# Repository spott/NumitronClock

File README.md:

# Numitron Clock

Top-board schematic and PCB layout for the four-tube clock described in the Obsidian note `electronics/Numitron Clock/Numitron Clock.md`, read on 2026-09-18. The detailed top-board decisions in that note supersede its older, general power and interconnect descriptions.

Open **[NumitronTop.kicad_pro](hardware/top-board/NumitronTop.kicad_pro)** in KiCad. The design was captured and checked with **KiCad 10.0.5**. All schematic symbols are included in the project-local library and embedded in the sheets.

## Review this revision

- [Power and inter-board interface](review/NumitronTop.svg)
- [Control and light sensor](review/NumitronTop-Logic%20_%20ambient%20light.svg)
- [Four tube drivers](review/NumitronTop-Four%20tube%20drivers.svg)
- [Connector and firmware contract](docs/interface.md)
- [Electrical design notes](docs/design.md)
- [Preliminary BOM](docs/bom.md)
- [Socket drawing and dimensions](docs/socket.md)
- [Provisional socket footprint](review/GZC9-A_B9A_Provisional.svg)
- [Top layout](review/NumitronTop-top.png), [underside layout](review/NumitronTop-bottom.png) and [dimensions / review notes](docs/placement.md)
- [Bring-up and ordering checks](docs/bring-up.md)
- [Archived component datasheets](datasheets/README.md)
- [ERC result](review/erc.rpt) and [exported-netlist audit](review/connectivity.txt)

The top board is placed and routed on a **110 × 40 mm working outline** with all 55 schematic parts, four M2.5 mounting positions, local power distribution and ground copper on both faces. The extra depth provides a separate underside strip for the wide SOIC drivers. The [layout notes](docs/placement.md) explain component placement, the perpendicular underside connector orientation and review process.

The GZC9-A socket footprint remains **provisional**, as explicitly authorized on 2026-09-25: 18 mm assumed tail circle, 0.5 mm estimated terminal thickness, 2.5 mm plated holes and 3.8 mm copper lands. Verify physical fit before ordering. Enclosure/cable fit, exact capacitor order codes and hardware measurements also remain assembly/release checks. **WWVB versus GPS belongs to the bottom board.**

The owner confirms the actual tubes are **marked DR2000 and have prefix decimal points**. The archived RCA table assigns that feature to DR2010 instead. The design preserves the requested HH.MM display and routes the eighth channel to pin 1; verify that decimal connection on the actual tubes before enabling it.

## Development

### ES100 time-source test firmware

The reusable async ES100 driver and Pico 2 breadboard program live in
[`firmware/`](firmware/README.md). Build and check them with the pinned firmware
toolchain (Rust/Cargo, Pico 2 target, flip-link and picotool are supplied by Nix):

```sh
nix develop .#firmware --command bash scripts/check_firmware.sh
```

The generated UF2 is `firmware/target/pico2-es100.uf2`. See the firmware guide for
wiring, BOOTSEL flashing, USB logs and the hardware test handoff. Physical
reception has not been validated; this does not decide WWVB versus GPS.

### Hardware tooling

Use the pinned Nix flake; no global package installation is required. KiCad is supplied by the existing local application installation on macOS. The flake pins the supporting Python, Poppler, SVG-rendering and local Freerouting tools, not that external KiCad application.

```sh
nix develop
bash scripts/review.sh
```

The review command runs KiCad ERC, audits the saved schematic's netlist and provisional socket footprint, exports schematic and footprint SVGs, and renders inspection PNGs under ignored `tmp/render/`. It does not regenerate or overwrite the schematic or footprint. Source PDFs and the socket drawing are archived in Git with their provenance and hashes.

`scripts/build_schematic.py --write` records the initial schematic capture and is deliberately opt-in: it **overwrites the native KiCad files**. After editing in KiCad, preserve those edits; reconcile the generator before using it again.

`hardware/top-board/socket-footprint.json` records the socket assumptions. `scripts/build_socket_footprint.py --write` captures them into the project-local `Numitron.pretty` library; reconcile manual footprint edits before regenerating. The schematic assigns `Numitron:GZC9-A_B9A_Provisional` to V1-V4.

`nix develop --command bash scripts/review_placement.sh` checks the saved PCB against the netlist, runs DRC with schematic parity and generates the top/bottom review drawings. It does not regenerate placement or routing. [board-drc.json](review/board-drc.json) and [placement-checks.txt](review/placement-checks.txt) retain the results.

`build_placement.py --write` is a one-time placement capture using KiCad's bundled Python; it refuses to discard routing without an explicit override. `placement.json` is the initial coordinate record, while the saved native board is authoritative. The power routing, local-router exchange and ground-fill helpers likewise require care around later CAD edits; do not run capture scripts just to review the design.

The repository covers the future whole clock. Its hardware design currently contains only the top board; the Pico 2 firmware is a separate time-receiver experiment. The bottom board will supply protected 5 V, regulated 3.3 V, the control interface and I2C pull-ups. Its schematic and layout remain future work.

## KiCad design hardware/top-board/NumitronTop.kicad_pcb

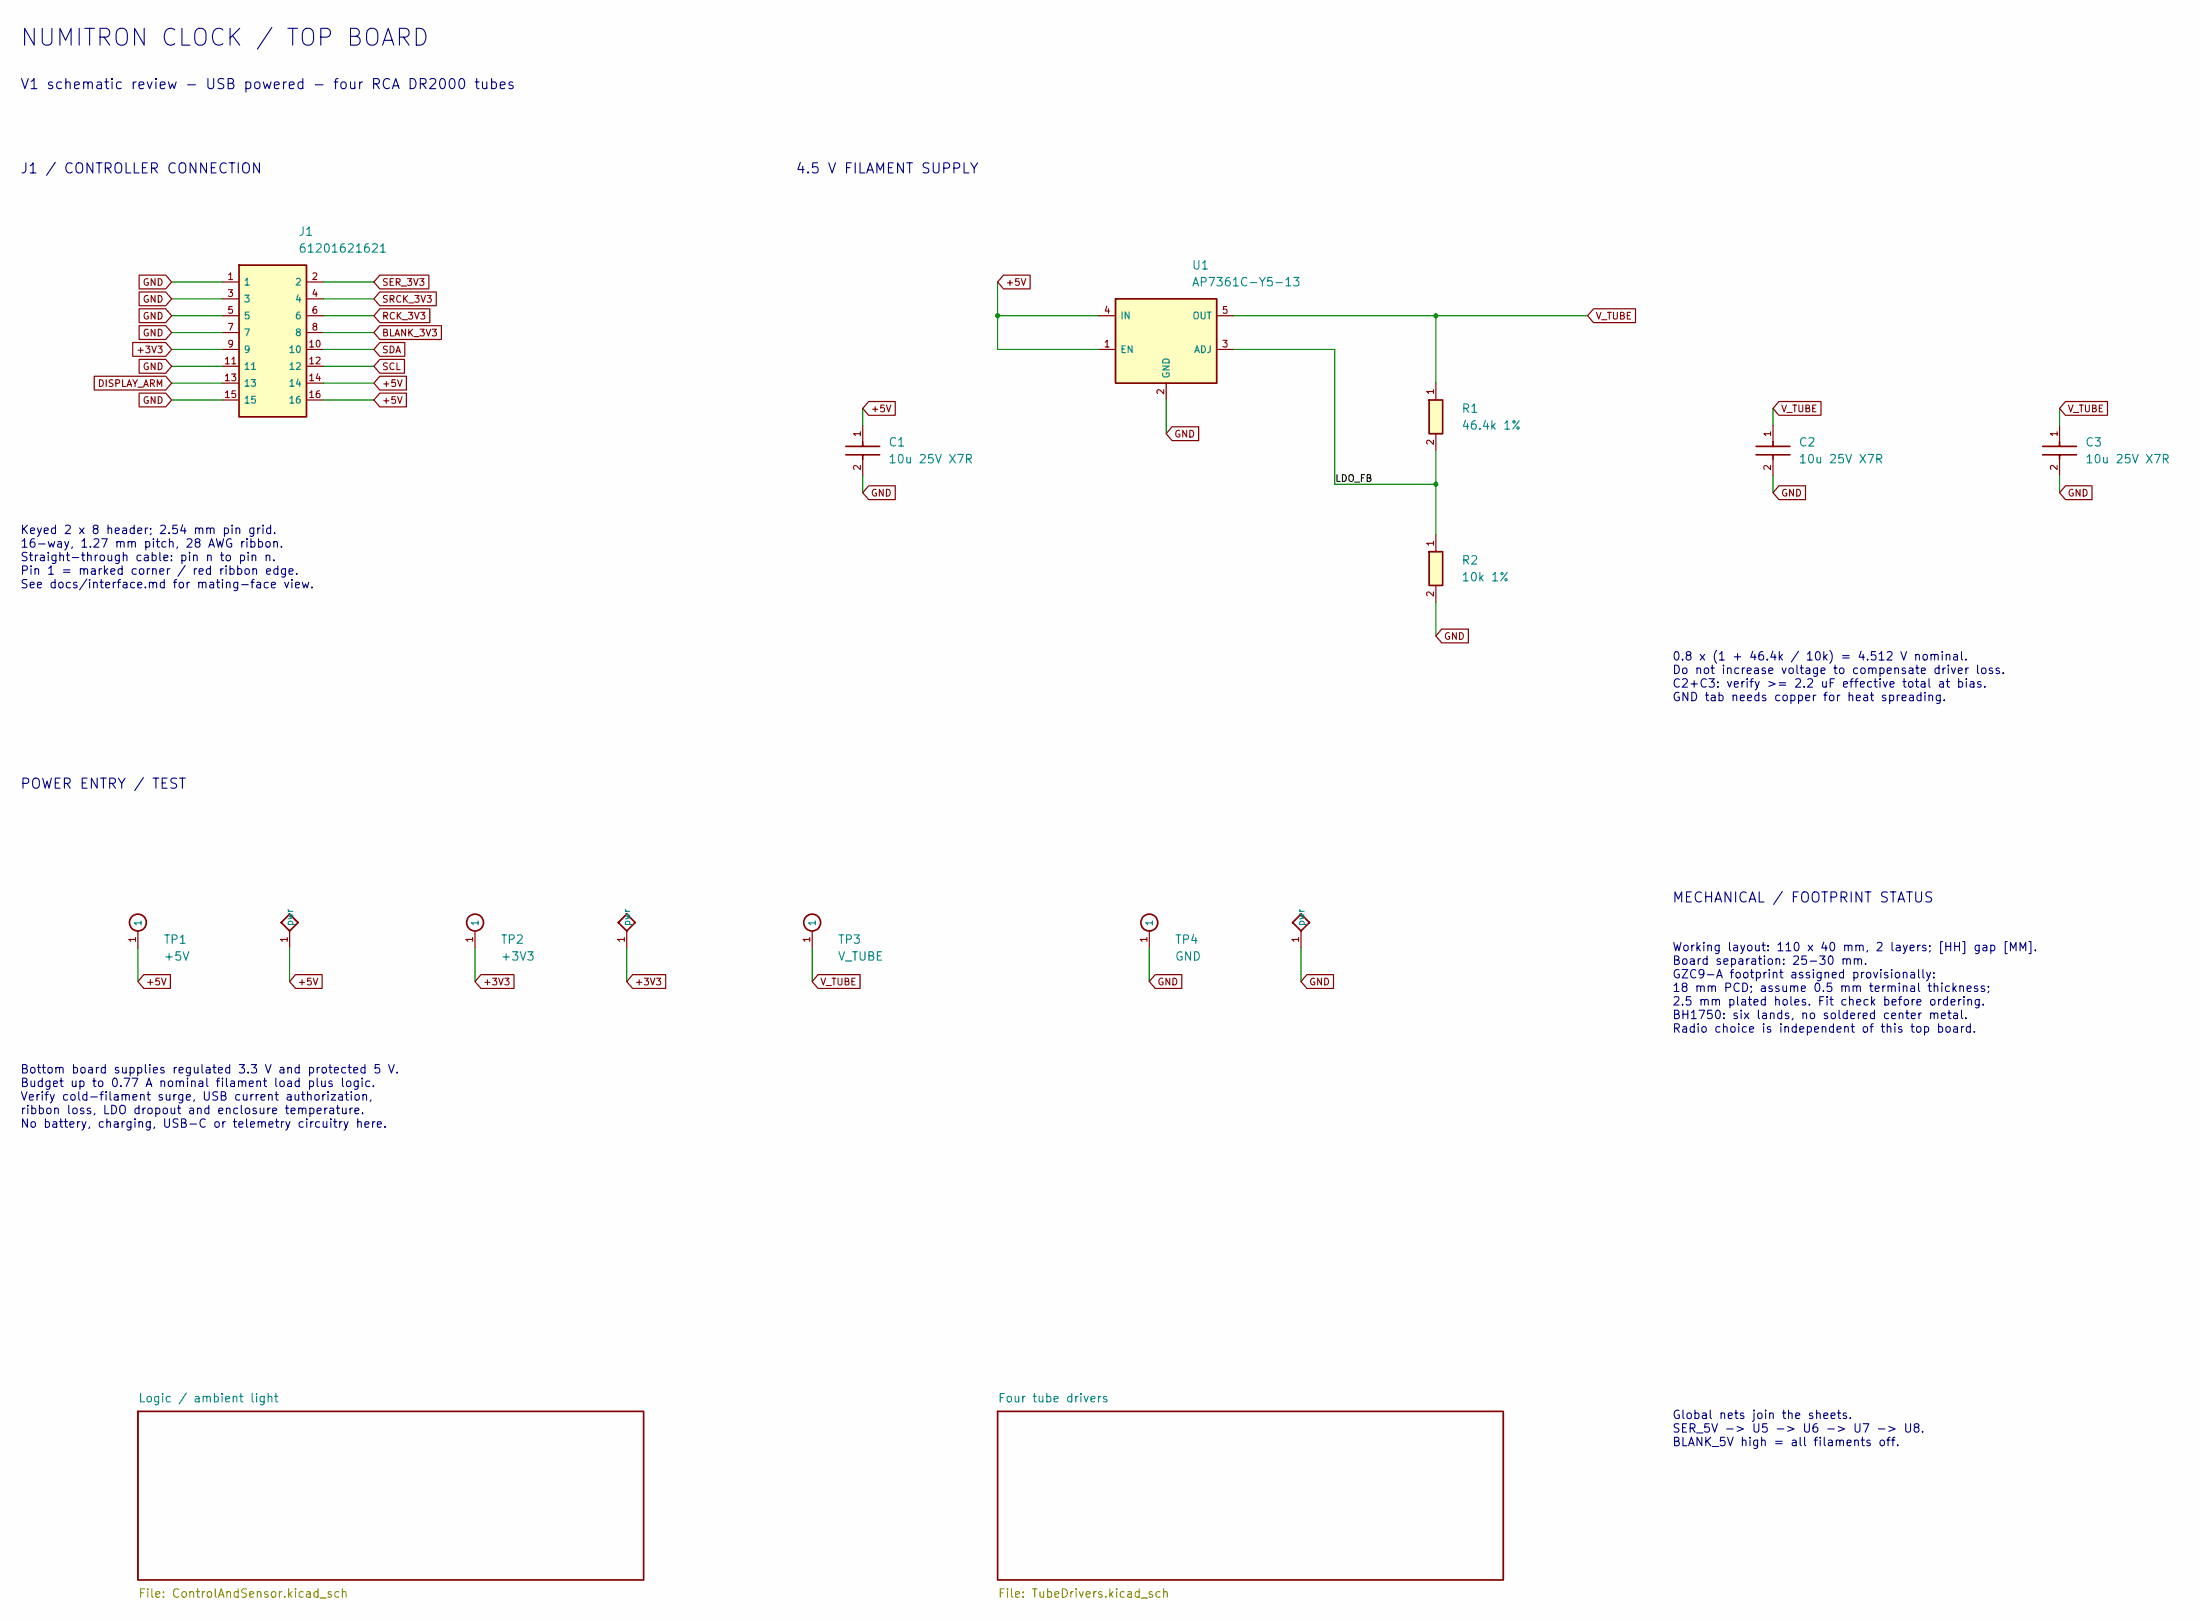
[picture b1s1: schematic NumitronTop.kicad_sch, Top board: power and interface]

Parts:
C1, C2, C3: 10u 25V X7R; C_1206_3216Metric
J1: 61201621621; Wurth_61201621621_2x08_P2.54mm; MPN 61201621621
R1: 46.4k 1%; R_0603_1608Metric; MPN RC0603FR-0746K4L
R2: 10k 1%; R_0603_1608Metric; MPN RC0603FR-0710KL
TP1: +5V; TestPoint_Pad_D1.5mm
TP2: +3V3; TestPoint_Pad_D1.5mm
TP3: V_TUBE; TestPoint_Pad_D1.5mm
TP4: GND; TestPoint_Pad_D1.5mm
U1: AP7361C-Y5-13; Diodes_SOT89-5_AP7361C; MPN AP7361C-Y5-13; LCSC C507885

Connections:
+3V3: J1.9, TP2.1; also elsewhere on the board
+5V: C1.1, J1.14, J1.16, TP1.1, U1.1 (EN), U1.4 (IN); also elsewhere on the board
/LDO_FB: R1.2, R2.1, U1.3 (ADJ)
BLANK_3V3: J1.8; also elsewhere on the board
DISPLAY_ARM: J1.13; also elsewhere on the board
GND: C1.2, C2.2, C3.2, J1.1, J1.3, J1.5, J1.7, J1.11, J1.15, R2.2, TP4.1, U1.2 (GND); also elsewhere on the board
RCK_3V3: J1.6; also elsewhere on the board
SCL: J1.12; also elsewhere on the board
SDA: J1.10; also elsewhere on the board
SER_3V3: J1.2; also elsewhere on the board
SRCK_3V3: J1.4; also elsewhere on the board
V_TUBE: C2.1, C3.1, R1.1, TP3.1, U1.5 (OUT); also elsewhere on the board

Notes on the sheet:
NUMITRON CLOCK / TOP BOARD
V1 schematic review - USB powered - four RCA DR2000 tubes
J1 / CONTROLLER CONNECTION
Keyed 2 x 8 header; 2.54 mm pin grid. 16-way, 1.27 mm pitch, 28 AWG ribbon. Straight-through cable: pin n to pin n. Pin 1 = marked corner / red ribbon edge. See docs/interface.md for mating-face view.
4.5 V FILAMENT SUPPLY
0.8 x (1 + 46.4k / 10k) = 4.512 V nominal. Do not increase voltage to compensate driver loss. C2+C3: verify >= 2.2 uF effective total at bias. GND tab needs copper for heat spreading.
POWER ENTRY / TEST
Bottom board supplies regulated 3.3 V and protected 5 V. Budget up to 0.77 A nominal filament load plus logic. Verify cold-filament surge, USB current authorization, ribbon loss, LDO dropout and enclosure temperature. No battery, charging, USB-C or telemetry circuitry here.
MECHANICAL / FOOTPRINT STATUS
Working layout: 110 x 40 mm, 2 layers; [HH] gap [MM]. Board separation: 25-30 mm. GZC9-A footprint assigned provisionally: 18 mm PCD; assume 0.5 mm terminal thickness; 2.5 mm plated holes. Fit check before ordering. BH1750: six lands, no soldered center metal. Radio choice is independent of this to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
Global nets join the sheets. SER_5V -> U5 -> U6 -> U7 -> U8. BLANK_5V high = all filaments off.

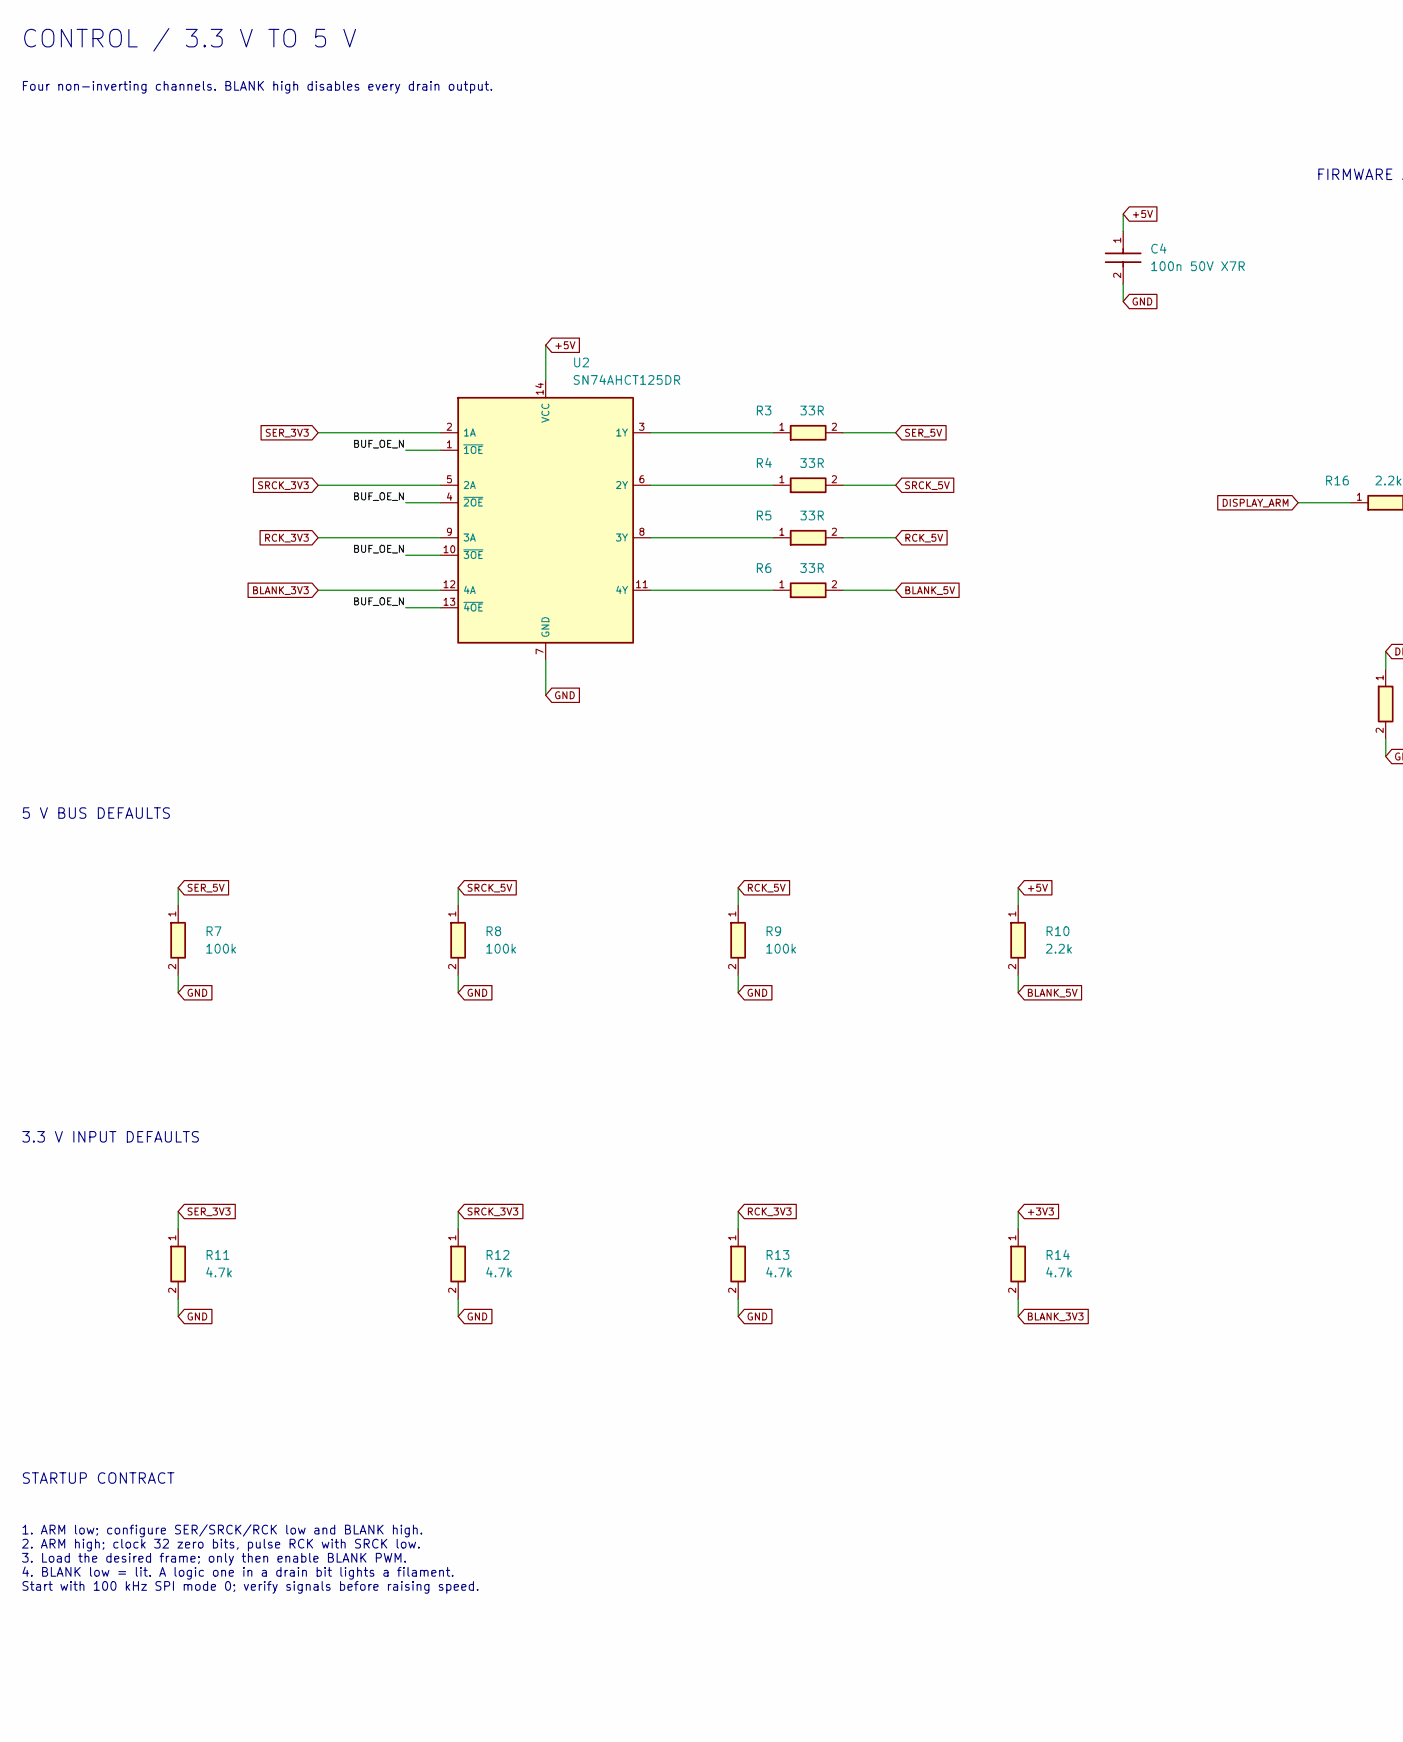
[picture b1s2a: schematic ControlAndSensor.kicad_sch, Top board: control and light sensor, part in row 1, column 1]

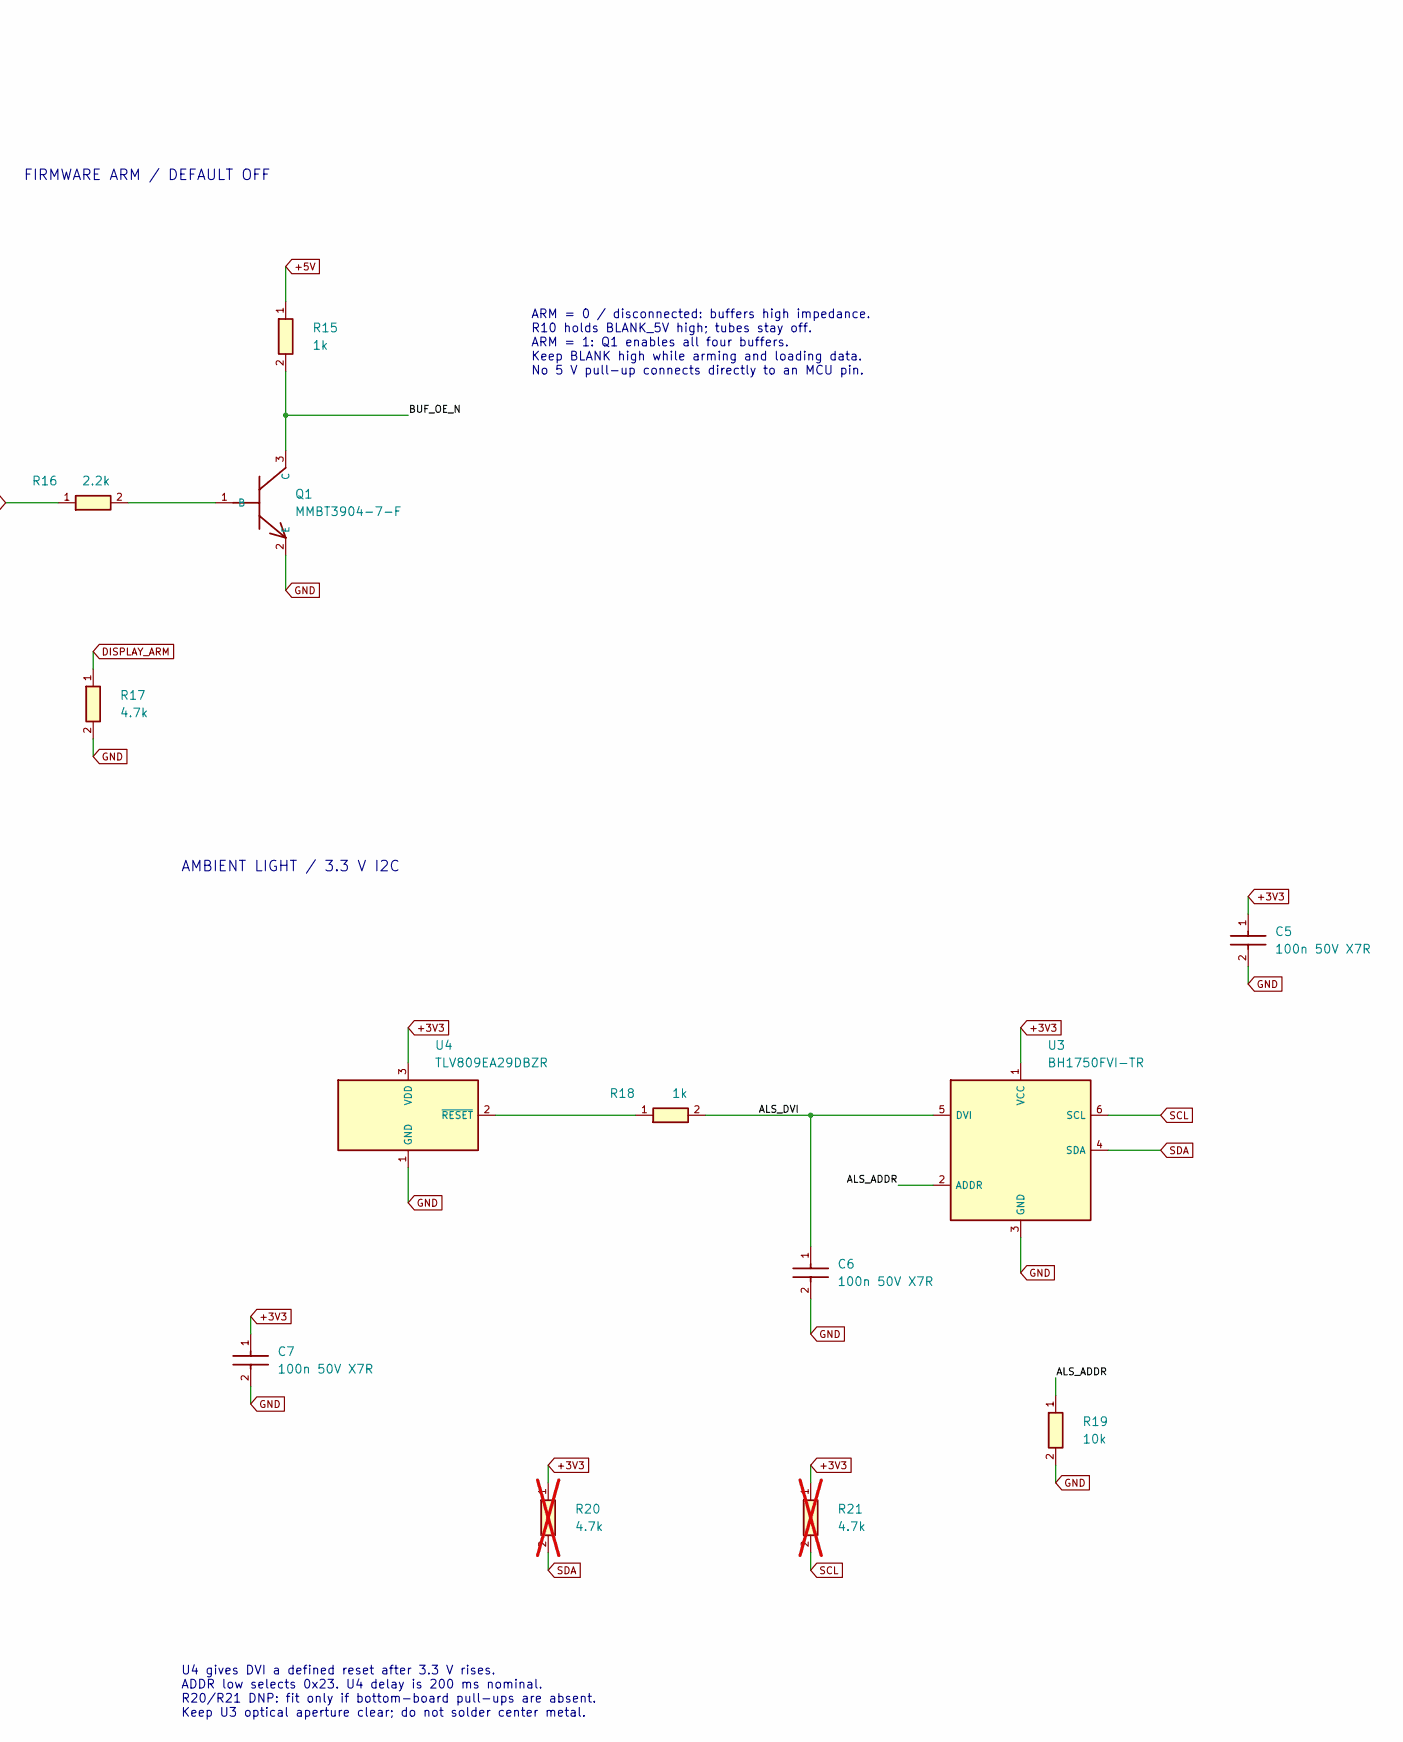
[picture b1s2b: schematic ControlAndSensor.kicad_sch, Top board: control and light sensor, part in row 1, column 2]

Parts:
C4, C5, C6, C7: 100n 50V X7R; C_0603_1608Metric
Q1: MMBT3904-7-F; SOT-23; MPN MMBT3904-7-F
R3, R4, R5, R6: 33R; R_0603_1608Metric; MPN RC0603FR-0733RL
R7, R8, R9: 100k; R_0603_1608Metric; MPN RC0603FR-07100KL
R10, R16: 2.2k; R_0603_1608Metric; MPN RC0603FR-072K2L
R11, R12, R13, R14, R17: 4.7k; R_0603_1608Metric; MPN RC0603FR-074K7L
R15, R18: 1k; R_0603_1608Metric; MPN RC0603FR-071KL
R19: 10k; R_0603_1608Metric; MPN RC0603FR-0710KL
R20, R21: 4.7k; R_0603_1608Metric; MPN RC0603FR-074K7L; not fitted
U2: SN74AHCT125DR; SOIC-14_3.9x8.7mm_P1.27mm; MPN SN74AHCT125DR
U3: BH1750FVI-TR; ROHM_WSOF6I_BH1750_NoCenterPad; MPN BH1750FVI-TR
U4: TLV809EA29DBZR; SOT-23; MPN TLV809EA29DBZR

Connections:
+3V3: C5.1, C7.1, R14.1, R20.1, R21.1, U3.1 (VCC), U4.3 (VDD); also elsewhere on the board
+5V: C4.1, R10.1, R15.1, U2.14 (VCC); also elsewhere on the board
/Logic / ambient light/ALS_ADDR: R19.1, U3.2 (ADDR)
/Logic / ambient light/ALS_DVI: C6.1, R18.2, U3.5 (DVI)
/Logic / ambient light/BUF_OE_N: Q1.3 (C), R15.2, U2.1 (~1OE), U2.4 (~2OE), U2.10 (~3OE), U2.13 (~4OE)
BLANK_3V3: R14.2, U2.12 (4A); also elsewhere on the board
BLANK_5V: R6.2, R10.2; also elsewhere on the board
DISPLAY_ARM: R16.1, R17.1; also elsewhere on the board
GND: C4.2, C5.2, C6.2, C7.2, Q1.2 (E), R7.2, R8.2, R9.2, R11.2, R12.2, R13.2, R17.2, R19.2, U2.7 (GND), U3.3 (GND), U4.1 (GND); also elsewhere on the board
unnamed: Q1.1 (B), R16.2
unnamed: R3.1, U2.3 (1Y)
unnamed: R4.1, U2.6 (2Y)
unnamed: R5.1, U2.8 (3Y)
unnamed: R6.1, U2.11 (4Y)
unnamed: R18.1, U4.2 (~RESET)
RCK_3V3: R13.1, U2.9 (3A); also elsewhere on the board
RCK_5V: R5.2, R9.1; also elsewhere on the board
SCL: R21.2, U3.6 (SCL); also elsewhere on the board
SDA: R20.2, U3.4 (SDA); also elsewhere on the board
SER_3V3: R11.1, U2.2 (1A); also elsewhere on the board
SER_5V: R3.2, R7.1; also elsewhere on the board
SRCK_3V3: R12.1, U2.5 (2A); also elsewhere on the board
SRCK_5V: R4.2, R8.1; also elsewhere on the board

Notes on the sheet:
CONTROL / 3.3 V TO 5 V
Four non-inverting channels. BLANK high disables every drain output.
FIRMWARE ARM / DEFAULT OFF
ARM = 0 / disconnected: buffers high impedance. R10 holds BLANK_5V high; tubes stay off. ARM = 1: Q1 enables all four buffers. Keep BLANK high while arming and loading data. No 5 V pull-up connects directly to an MCU pin.
5 V BUS DEFAULTS
3.3 V INPUT DEFAULTS
STARTUP CONTRACT
1. ARM low; configure SER/SRCK/RCK low and BLANK high. 2. ARM high; clock 32 zero bits, pulse RCK with SRCK low. 3. Load the desired frame; only then enable BLANK PWM. 4. BLANK low = lit. A logic one in a drain bit lights a filament. Start with 100 kHz SPI mode 0; verify signals before raising spee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
AMBIENT LIGHT / 3.3 V I2C
U4 gives DVI a defined reset after 3.3 V rises. ADDR low selects 0x23. U4 delay is 200 ms nominal. R20/R21 DNP: fit only if bottom-board pull-ups are absent. Keep U3 optical aperture clear; do not solder center metal.

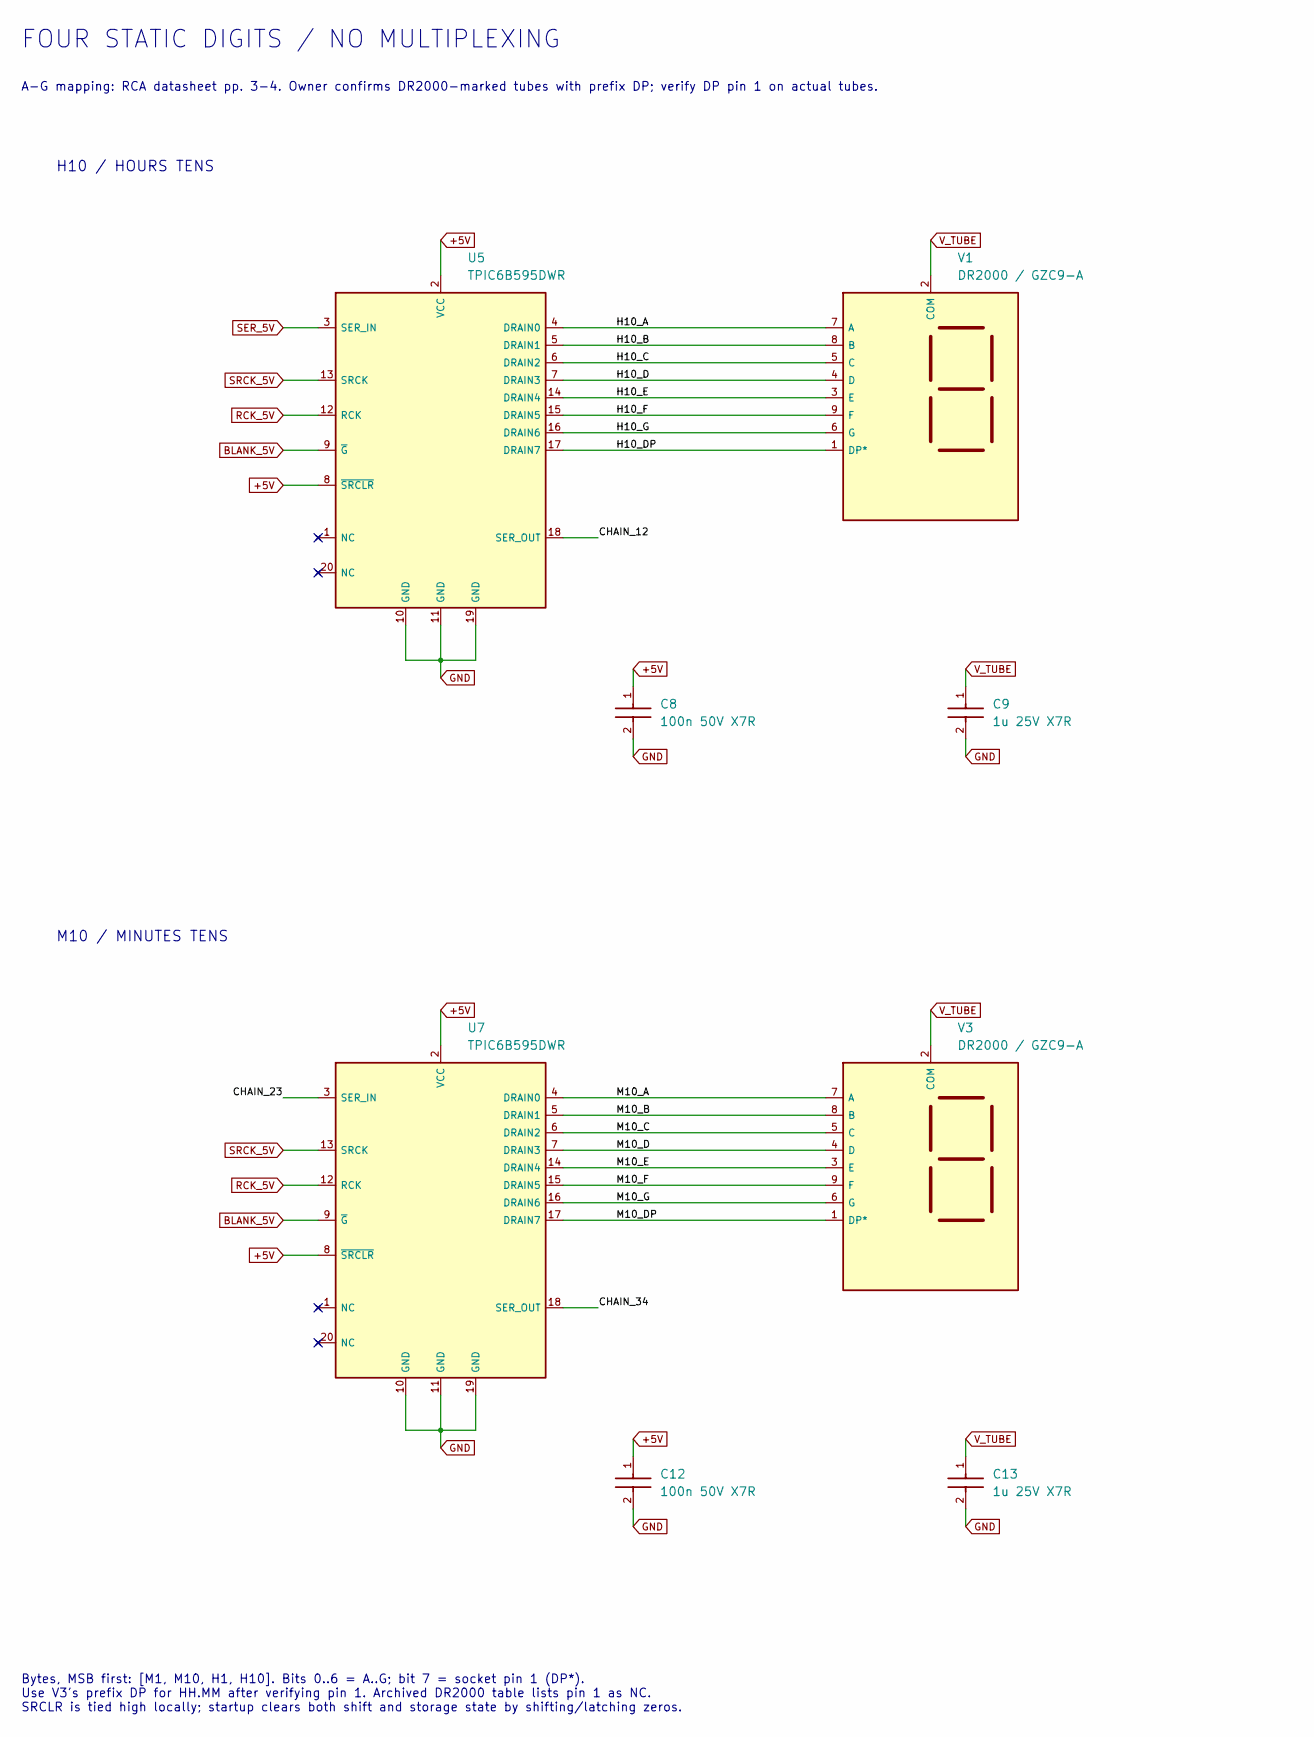
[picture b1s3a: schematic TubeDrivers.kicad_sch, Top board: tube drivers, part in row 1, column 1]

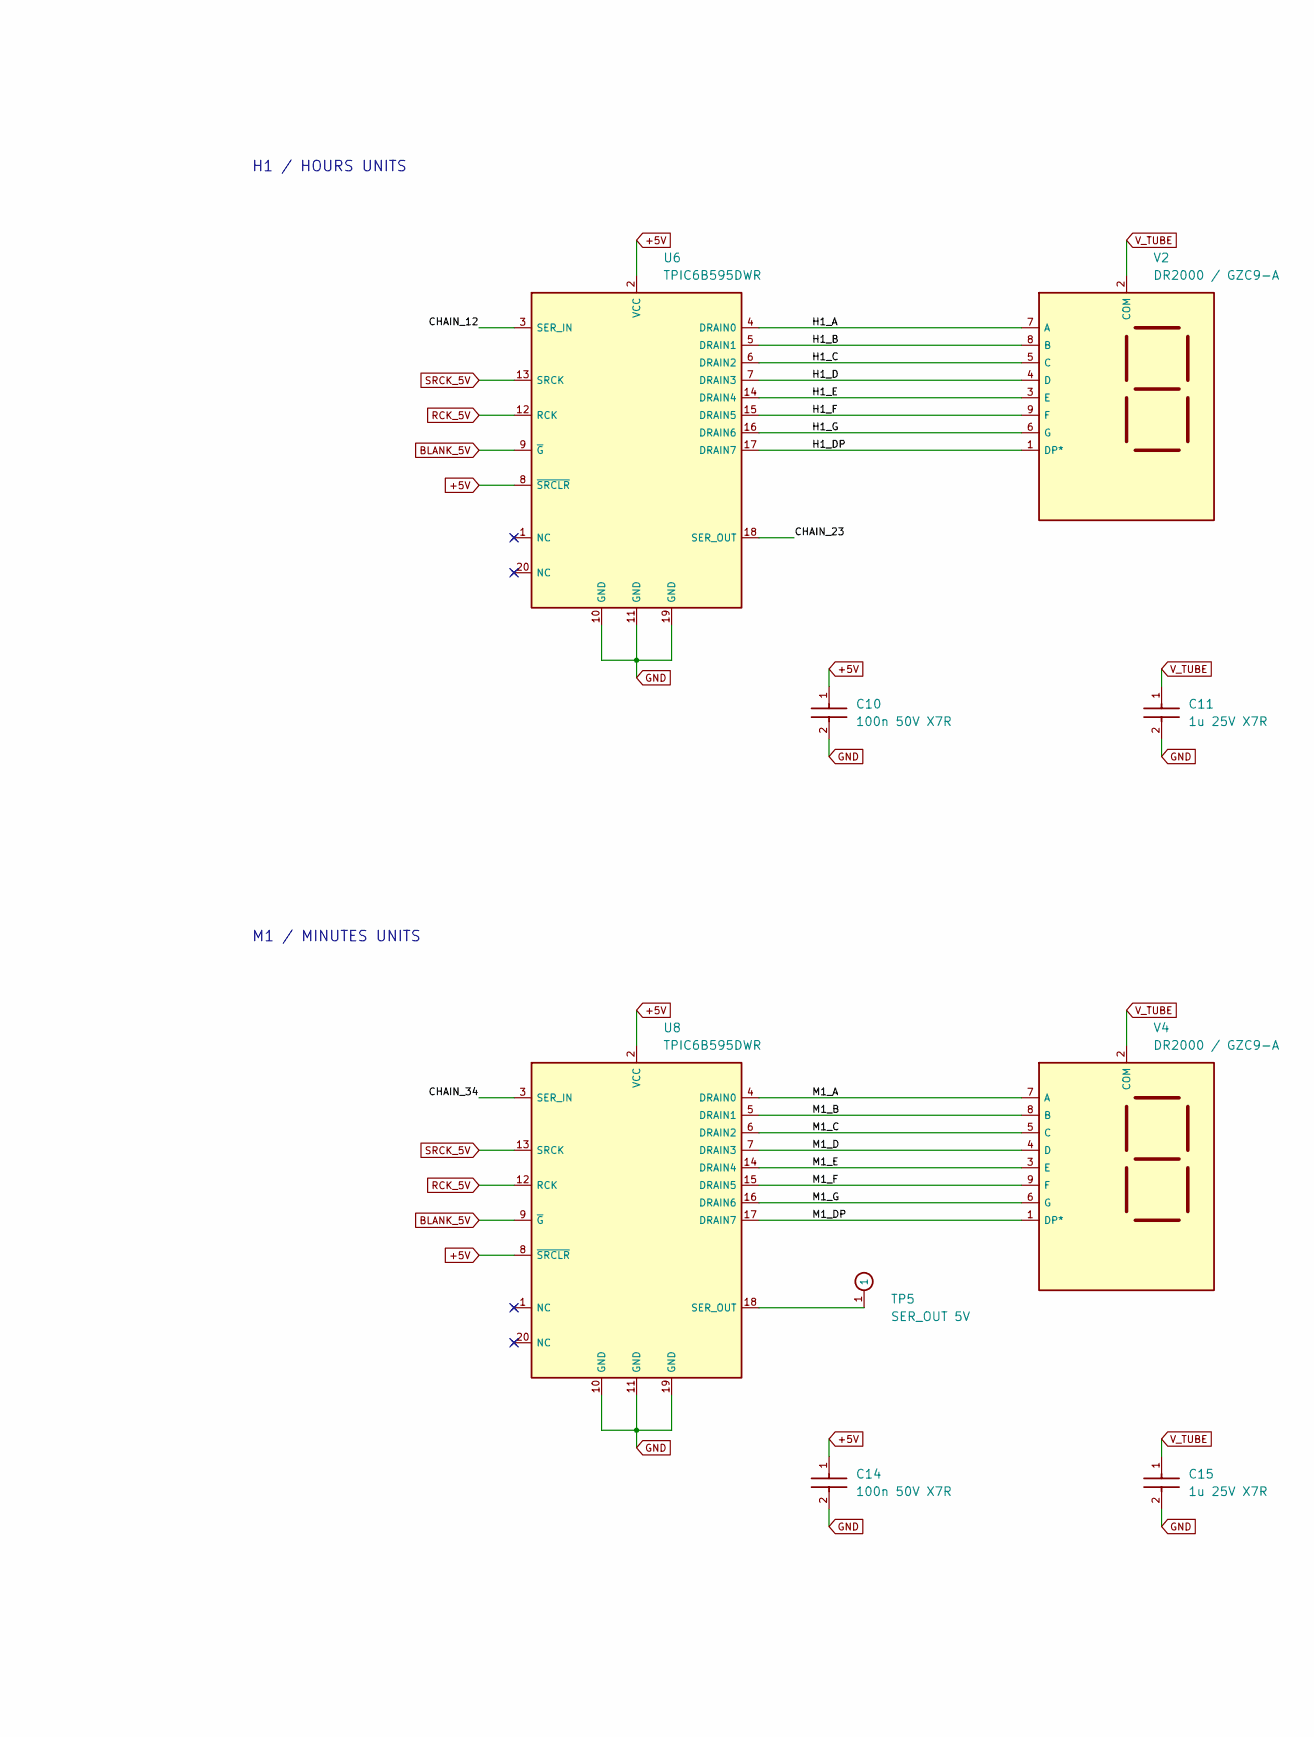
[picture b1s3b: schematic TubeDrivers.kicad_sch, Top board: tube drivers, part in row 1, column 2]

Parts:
C8, C10, C12, C14: 100n 50V X7R; C_0603_1608Metric
C9, C11, C13, C15: 1u 25V X7R; C_0805_2012Metric
TP5: SER_OUT 5V; TestPoint_Pad_D1.5mm
U5, U6, U7, U8: TPIC6B595DWR; SOIC-20W_7.5x12.8mm_P1.27mm; MPN TPIC6B595DWR
V1, V2, V3, V4: DR2000 / GZC9-A; GZC9-A_B9A_Provisional; MPN DR2000

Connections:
+5V: C8.1, C10.1, C12.1, C14.1, U5.2 (VCC), U5.8 (~SRCLR), U6.2 (VCC), U6.8 (~SRCLR), U7.2 (VCC), U7.8 (~SRCLR), U8.2 (VCC), U8.8 (~SRCLR); also elsewhere on the board
/Four tube drivers/CHAIN_12: U5.18 (SER_OUT), U6.3 (SER_IN)
/Four tube drivers/CHAIN_23: U6.18 (SER_OUT), U7.3 (SER_IN)
/Four tube drivers/CHAIN_34: U7.18 (SER_OUT), U8.3 (SER_IN)
/Four tube drivers/H1_A: U6.4 (DRAIN0), V2.7 (A)
/Four tube drivers/H1_B: U6.5 (DRAIN1), V2.8 (B)
/Four tube drivers/H1_C: U6.6 (DRAIN2), V2.5 (C)
/Four tube drivers/H1_D: U6.7 (DRAIN3), V2.4 (D)
/Four tube drivers/H1_DP: U6.17 (DRAIN7), V2.1 (DP*)
/Four tube drivers/H1_E: U6.14 (DRAIN4), V2.3 (E)
/Four tube drivers/H1_F: U6.15 (DRAIN5), V2.9 (F)
/Four tube drivers/H1_G: U6.16 (DRAIN6), V2.6 (G)
/Four tube drivers/H10_A: U5.4 (DRAIN0), V1.7 (A)
/Four tube drivers/H10_B: U5.5 (DRAIN1), V1.8 (B)
/Four tube drivers/H10_C: U5.6 (DRAIN2), V1.5 (C)
/Four tube drivers/H10_D: U5.7 (DRAIN3), V1.4 (D)
/Four tube drivers/H10_DP: U5.17 (DRAIN7), V1.1 (DP*)
/Four tube drivers/H10_E: U5.14 (DRAIN4), V1.3 (E)
/Four tube drivers/H10_F: U5.15 (DRAIN5), V1.9 (F)
/Four tube drivers/H10_G: U5.16 (DRAIN6), V1.6 (G)
/Four tube drivers/M1_A: U8.4 (DRAIN0), V4.7 (A)
/Four tube drivers/M1_B: U8.5 (DRAIN1), V4.8 (B)
/Four tube drivers/M1_C: U8.6 (DRAIN2), V4.5 (C)
/Four tube drivers/M1_D: U8.7 (DRAIN3), V4.4 (D)
/Four tube drivers/M1_DP: U8.17 (DRAIN7), V4.1 (DP*)
/Four tube drivers/M1_E: U8.14 (DRAIN4), V4.3 (E)
/Four tube drivers/M1_F: U8.15 (DRAIN5), V4.9 (F)
/Four tube drivers/M1_G: U8.16 (DRAIN6), V4.6 (G)
/Four tube drivers/M10_A: U7.4 (DRAIN0), V3.7 (A)
/Four tube drivers/M10_B: U7.5 (DRAIN1), V3.8 (B)
/Four tube drivers/M10_C: U7.6 (DRAIN2), V3.5 (C)
/Four tube drivers/M10_D: U7.7 (DRAIN3), V3.4 (D)
/Four tube drivers/M10_DP: U7.17 (DRAIN7), V3.1 (DP*)
/Four tube drivers/M10_E: U7.14 (DRAIN4), V3.3 (E)
/Four tube drivers/M10_F: U7.15 (DRAIN5), V3.9 (F)
/Four tube drivers/M10_G: U7.16 (DRAIN6), V3.6 (G)
BLANK_5V: U5.9 (~G), U6.9 (~G), U7.9 (~G), U8.9 (~G); also elsewhere on the board
GND: C8.2, C9.2, C10.2, C11.2, C12.2, C13.2, C14.2, C15.2, U5.10 (GND), U5.11 (GND), U5.19 (GND), U6.10 (GND), U6.11 (GND), U6.19 (GND), U7.10 (GND), U7.11 (GND), U7.19 (GND), U8.10 (GND), U8.11 (GND), U8.19 (GND); also elsewhere on the board
unnamed: TP5.1, U8.18 (SER_OUT)
RCK_5V: U5.12 (RCK), U6.12 (RCK), U7.12 (RCK), U8.12 (RCK); also elsewhere on the board
SER_5V: U5.3 (SER_IN); also elsewhere on the board
SRCK_5V: U5.13 (SRCK), U6.13 (SRCK), U7.13 (SRCK), U8.13 (SRCK); also elsewhere on the board
V_TUBE: C9.1, C11.1, C13.1, C15.1, V1.2 (COM), V2.2 (COM), V3.2 (COM), V4.2 (COM); also elsewhere on the board

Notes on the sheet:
FOUR STATIC DIGITS / NO MULTIPLEXING
A-G mapping: RCA datasheet pp. 3-4. Owner confirms DR2000-marked tubes with prefix DP; verify DP pin 1 on actual tubes.
H10 / HOURS TENS
H1 / HOURS UNITS
M10 / MINUTES TENS
M1 / MINUTES UNITS
Bytes, MSB first: [M1, M10, H1, H10]. Bits 0..6 = A..G; bit 7 = socket pin 1 (DP*). Use V3's prefix DP for HH.MM after verifying pin 1. Archived DR2000 table lists pin 1 as NC. SRCLR is tied high locally; startup clears both shift and storage state by shifting/latching zeros.
